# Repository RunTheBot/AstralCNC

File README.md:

# AstralCNC

A Replacement board for the Larken **StarCNC** controller. Built around the RPI Pico, this board is designed with safety and flexibility in mind, allowing for easy integration with external stepper drivers and digital inputs.

Powered by the Raspberry Pi Pico and GRBL-HAL.

Made to referbrish a Larken 24/24 router at my school that is over 25 years old.

# Features
- Supports up to 8 external stepper drivers (5v IO, Step/Dir)
- Supports up to 8 external digital inputs (3.3v IO)
- 5v IO can be switched to 3.3v IO
- 3.3v IO can be switched to 5v IO (for external stepper drivers)
- Built-in 12v regulator for powering all components
- Hardware level emergency stop
  - Emergency stop is not relient on software, ensuring that it works even if the software crashes as the stepper drivers put out a good ammount of EMI
- Hardware level reset button
  - Reset after an emergency stop is not relient on software, ensuring that the machine will remain stopped until it is manually reset
- 4 Analog inputs (ADC)
- All IO is PWM capable

# Images

# BOM

| Name                                           | Quantity | Single Unit Price | Total Price | URL/LCSC                                   | FALSE | Vendor (LCSC unless otheriwse indicated) |
|------------------------------------------------|----------|-------------------|-------------|--------------------------------------------|-------|------------------------------------------|
| Electronics                                    |          |                   |             |                                            | FALSE |                                          |
| 47pF                                           | 1        | N/A               | $0.29       | C105622                                    | FALSE |                                          |
| 0.1uF                                          | 1        | N/A               |             |                                            | FALSE | With My other two projects               |
| 22uF                                           | 2        | N/A               | $0.17       | C59461                                     | FALSE |                                          |
| 4.7uF                                          | 2        | N/A               | $0.15       | C69335                                     | FALSE |                                          |
| Molex_KK-254_AE-6410-02A_1x02_P2.54mm_Vertical | 1        | N/A               | $0.40       | C5447965                                   | FALSE |                                          |
| Molex_KK-254_AE-6410-10A_1x10_P2.54mm_Vertical | 1        | N/A               | $0.39       | C30169                                     | FALSE |                                          |
| PinHeader_2x04_P2.54mm_Vertical                | 1        | N/A               | $0.39       | C2829882                                   | FALSE |                                          |
| PinHeader_1x04_P2.54mm_Vertical                | 7        | N/A               | $0.42       | C2935910                                   | FALSE |                                          |
| Molex_KK-254_AE-6410-03A_1x03_P2.54mm_Vertical | 4        | N/A               | $0.71       | C29275                                     | FALSE |                                          |
| 6.8UH                                          | 1        | N/A               | $1.18       | C5296375                                   | FALSE |                                          |
| BC847                                          | 3        | N/A               | $0.46       | C57668                                     | FALSE |                                          |
| 220k                                           | 1        | N/A               | $0.10       | C22961                                     | FALSE |                                          |
| 41.2k                                          | 1        | N/A               | $0.10       | C2930101                                   | FALSE |                                          |
| 93.1k                                          | 1        | N/A               | $0.10       | C2933266                                   | FALSE |                                          |
| 22k                                            | 1        | N/A               | $0.09       | C2907015                                   | FALSE |                                          |
| 10k                                            | 6        | N/A               |             |                                            | FALSE | With My other two projects               |
| AP63357                                        | 1        | N/A               | $0.52       | C2158014                                   | FALSE |                                          |
| 74HC244                                        | 2        | N/A               | $0.77       | C5623                                      | FALSE |                                          |
| RP2350_Stamp                                   | 1        | N/A               | $12.05      | https://lectronz.com/products/rp2350-stamp | FALSE |                                          |
| TXS0108EPW                                     | 2        | N/A               | $1.12       | C17206                                     | FALSE |                                          |
| MOLEX 22013037                                 | 4        |                   | $0.27       | C22451182                                  | FALSE |                                          |
| Molex 2759 seris                               | 12       |                   | $0.24       | C22451180                                  | FALSE |                                          |
| PCB - JLC                                      |          |                   | $9.00       |                                            |       |                                          |
| LCSC - Shipping and handling                   |          |                   | $17.16      |                                            |       |                                          |
| lectronz                                       |          |                   | $17.79      |                                            |       |                                          |
| JLC - Shipping                                 |          |                   | $8.23       |                                            |       |                                          |
|                                                |          |                   |             |                                            |       |                                          |
|                                                |          |                   |             |                                            |       |                                          |
|                                                |          |                   |             |                                            |       |                                          |
|                                                |          |                   |             |                                            |       |                                          |
|                                                |          |                   |             |                                            |       |                                          |
|                                                |          |                   |             |                                            |       |                                          |
|                                                |          |                   |             |                                            |       |                                          |
|                                                |          |                   |             | CAD                                        |       |                                          |
|                                                |          |                   | $72.10      | USD                                        |       |                                          |
|                                                |          |                   | $72.10      | Total - USD                                |       |                                          |

Why is shipping so expensive? 😭

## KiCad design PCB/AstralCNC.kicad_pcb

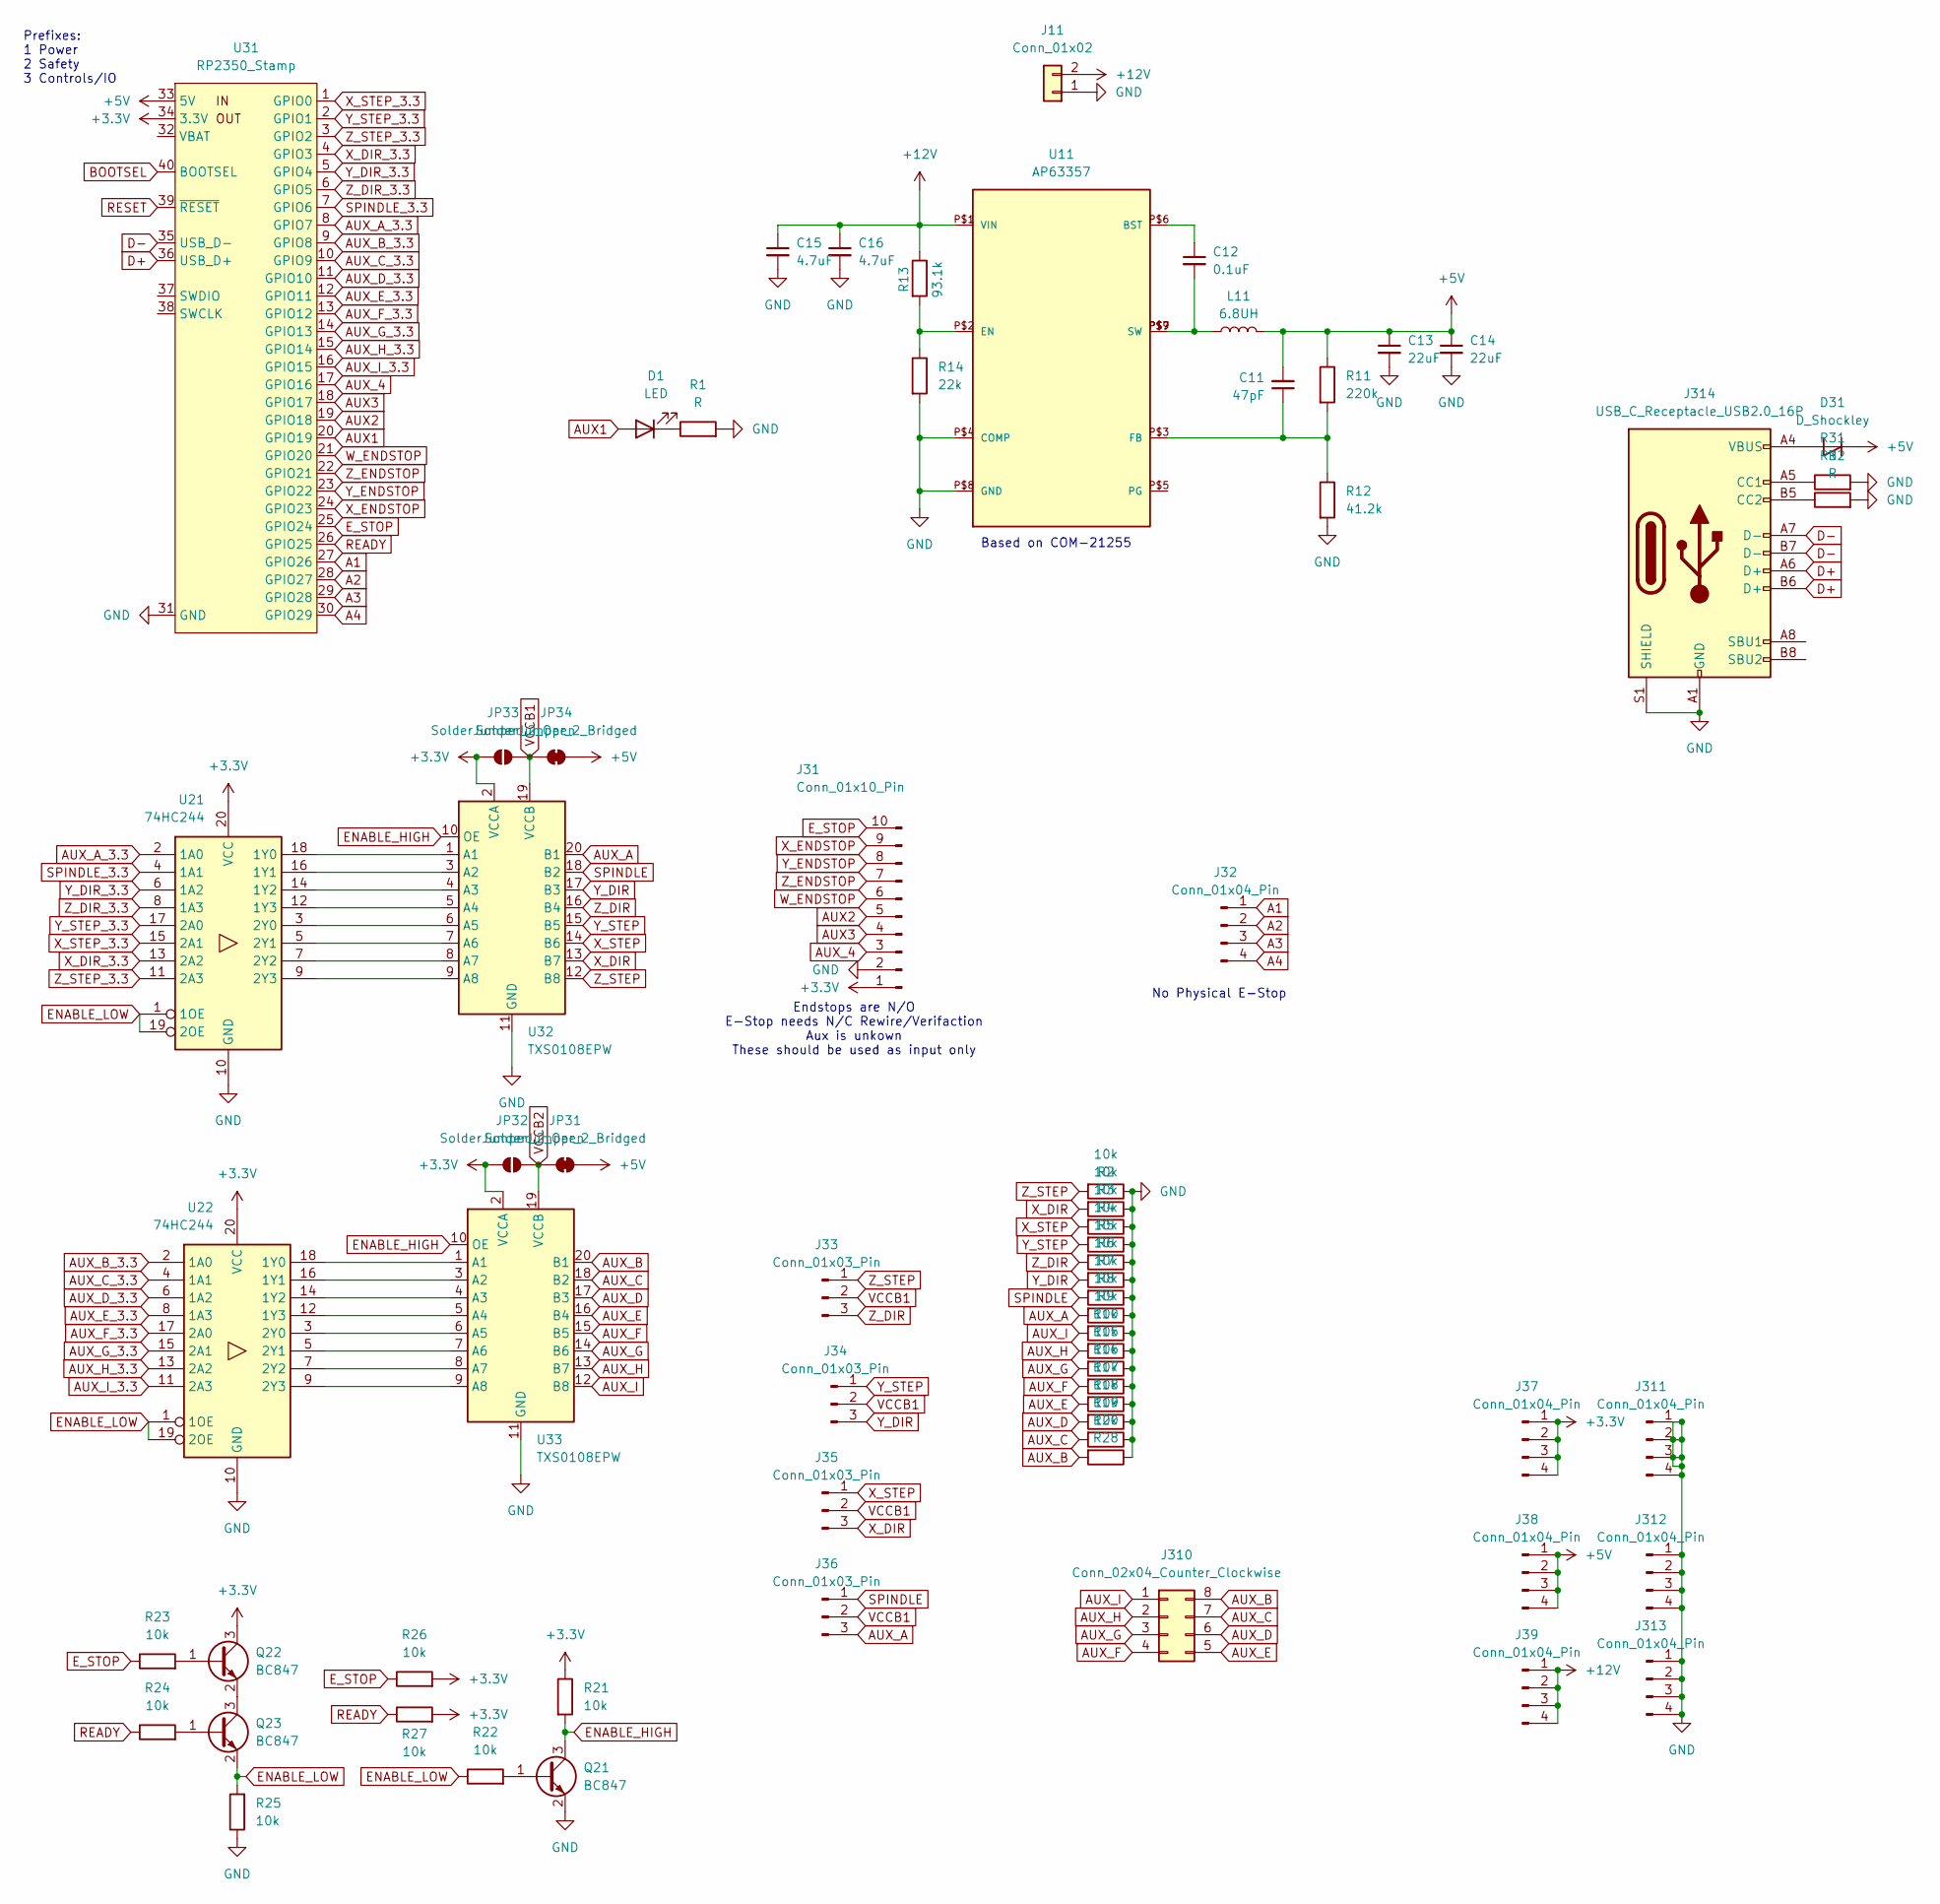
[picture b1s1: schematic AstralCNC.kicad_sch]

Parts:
C11: 47pF; C_0603_1608Metric_Pad1.08x0.95mm_HandSolder
C12: 0.1uF; C_0805_2012Metric_Pad1.18x1.45mm_HandSolder
C13, C14: 22uF; C_0603_1608Metric_Pad1.08x0.95mm_HandSolder
C15, C16: 4.7uF; C_0603_1608Metric_Pad1.08x0.95mm_HandSolder
D1: LED; PinHeader_1x02_P2.54mm_Vertical
D31: D_Shockley; D_SMA_Handsoldering
J11: Conn_01x02; Molex_KK-254_AE-6410-02A_1x02_P2.54mm_Vertical
J31: Conn_01x10_Pin; Molex_KK-254_AE-6410-10A_1x10_P2.54mm_Vertical
J32, J37, J38, J39, J311, J312, J313: Conn_01x04_Pin; PinHeader_1x04_P2.54mm_Vertical
J33, J34, J35, J36: Conn_01x03_Pin; Molex_KK-254_AE-6410-03A_1x03_P2.54mm_Vertical
J310: Conn_02x04_Counter_Clockwise; PinHeader_2x04_P2.54mm_Vertical
J314: USB_C_Receptacle_USB2.0_16P; USB_C_Receptacle_G-Switch_GT-USB-7010ASV
JP31, JP34: SolderJumper_2_Bridged; SolderJumper-2_P1.3mm_Bridged_RoundedPad1.0x1.5mm
JP32, JP33: SolderJumper_2_Open; SolderJumper-2_P1.3mm_Open_RoundedPad1.0x1.5mm
L11: 6.8UH; L_Chilisin_BMRA00050530
Q21, Q22, Q23: BC847; SOT-23
R1, R31, R32: R; C_0603_1608Metric_Pad1.08x0.95mm_HandSolder
R2, R3, R4, R5, R6, R7, R8, R9, R10, R15, R16, R17, R18, R19, R20, R21, R22, R23, R24, R25, R26, R27, R28: 10k; C_0603_1608Metric_Pad1.08x0.95mm_HandSolder
R11: 220k; C_0603_1608Metric_Pad1.08x0.95mm_HandSolder
R12: 41.2k; C_0603_1608Metric_Pad1.08x0.95mm_HandSolder
R13: 93.1k; C_0603_1608Metric_Pad1.08x0.95mm_HandSolder
R14: 22k; C_0603_1608Metric_Pad1.08x0.95mm_HandSolder
U11: AP63357; V-DFN3020-13
U21, U22: 74HC244; TSSOP-20_4.4x6.5mm_P0.65mm
U31: RP2350_Stamp; RP2xxx_Stamp_THT
U32, U33: TXS0108EPW; TSSOP-20_4.4x6.5mm_P0.65mm

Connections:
+3.3V: J31.1, J37.1, J37.2, J37.3, J37.4, JP32.1 (A), JP33.1 (A), Q22.3 (C), R21.1, R26.2, R27.2, U21.20 (VCC), U22.20 (VCC), U31.34 (3.3V), U32.2 (VCCA), U33.2 (VCCA)
+5V: C11.2, C13.1, C14.1, D31.1 (K), J38.1, J38.2, J38.3, J38.4, JP31.2 (B), JP34.2 (B), L11.2, R11.1, U31.33 (5V)
+12V: C15.1, C16.1, J11.2, J39.1, J39.2, J39.3, J39.4, R13.1, U11.P$1 (VIN)
A1: J32.1, U31.27 (GPIO26)
A2: J32.2, U31.28 (GPIO27)
A3: J32.3, U31.29 (GPIO28)
A4: J32.4, U31.30 (GPIO29)
AUX1: D1.2 (A), U31.20 (GPIO19)
AUX2: J31.5, U31.19 (GPIO18)
AUX3: J31.4, U31.18 (GPIO17)
AUX_4: J31.3, U31.17 (GPIO16)
AUX_A: J36.3, R9.2, U32.20 (B1)
AUX_A_3.3: U21.2 (1A0), U31.8 (GPIO7)
AUX_B: J310.8, R28.2, U33.20 (B1)
AUX_B_3.3: U22.2 (1A0), U31.9 (GPIO8)
AUX_C: J310.7, R20.2, U33.18 (B2)
AUX_C_3.3: U22.4 (1A1), U31.10 (GPIO9)
AUX_D: J310.6, R19.2, U33.17 (B3)
AUX_D_3.3: U22.6 (1A2), U31.11 (GPIO10)
AUX_E: J310.5, R18.2, U33.16 (B4)
AUX_E_3.3: U22.8 (1A3), U31.12 (GPIO11)
AUX_F: J310.4, R17.2, U33.15 (B5)
AUX_F_3.3: U22.17 (2A0), U31.13 (GPIO12)
AUX_G: J310.3, R16.2, U33.14 (B6)
AUX_G_3.3: U22.15 (2A1), U31.14 (GPIO13)
AUX_H: J310.2, R15.2, U33.13 (B7)
AUX_H_3.3: U22.13 (2A2), U31.15 (GPIO14)
AUX_I: J310.1, R10.2, U33.12 (B8)
AUX_I_3.3: U22.11 (2A3), U31.16 (GPIO15)
BOOTSEL: U31.40 (BOOTSEL)
D+: J314.A6 (D+), J314.B6 (D+), U31.36 (USB_D+)
D-: J314.A7 (D-), J314.B7 (D-), U31.35 (USB_D-)
ENABLE_HIGH: Q21.3 (C), R21.2, U32.10 (OE), U33.10 (OE)
ENABLE_LOW: Q23.2 (E), R22.1, R25.2, U21.1 (1OE), U21.19 (2OE), U22.1 (1OE), U22.19 (2OE)
E_STOP: J31.10, R23.1, R26.1, U31.25 (GPIO24)
GND: C13.2, C14.2, C15.2, C16.2, J11.1, J31.2, J311.1, J311.2, J311.3, J311.4, J312.1, J312.2, J312.3, J312.4, J313.1, J313.2, J313.3, J313.4, J314.A1 (GND), J314.A12 (GND), J314.B1 (GND), J314.B12 (GND), J314.S1 (SHIELD), Q21.2 (E), R1.2, R2.1, R3.1, R4.1, R5.1, R6.1, R7.1, R8.1, R9.1, R10.1, R12.2, R14.2, R15.1, R16.1, R17.1, R18.1, R19.1, R20.1, R25.1, R28.1, R31.2, R32.2, U11.P$4 (COMP), U11.P$8 (GND), U21.10 (GND), U22.10 (GND), U31.31 (GND), U32.11 (GND), U33.11 (GND)
unnamed: C12.2, L11.1, U11.P$7 (SW), U11.P$9 (SW)
unnamed: D1.1 (K), R1.1
unnamed: D31.2 (A), J314.A4 (VBUS), J314.A9 (VBUS), J314.B4 (VBUS), J314.B9 (VBUS)
unnamed: J314.A5 (CC1), R31.1
unnamed: J314.B5 (CC2), R32.1
unnamed: Q21.1 (B), R22.2
unnamed: Q22.1 (B), R23.2
unnamed: Q22.2 (E), Q23.3 (C)
unnamed: Q23.1 (B), R24.2
unnamed: C12.1, U11.P$6 (BST)
unnamed: R13.2, R14.1, U11.P$2 (EN)
unnamed: C11.1, R11.2, R12.1, U11.P$3 (FB)
unnamed: U21.18 (1Y0), U32.1 (A1)
unnamed: U21.16 (1Y1), U32.3 (A2)
unnamed: U21.14 (1Y2), U32.4 (A3)
unnamed: U21.12 (1Y3), U32.5 (A4)
unnamed: U21.3 (2Y0), U32.6 (A5)
unnamed: U21.5 (2Y1), U32.7 (A6)
unnamed: U21.7 (2Y2), U32.8 (A7)
unnamed: U21.9 (2Y3), U32.9 (A8)
unnamed: U22.18 (1Y0), U33.1 (A1)
unnamed: U22.16 (1Y1), U33.3 (A2)
unnamed: U22.14 (1Y2), U33.4 (A3)
unnamed: U22.12 (1Y3), U33.5 (A4)
unnamed: U22.3 (2Y0), U33.6 (A5)
unnamed: U22.5 (2Y1), U33.7 (A6)
unnamed: U22.7 (2Y2), U33.8 (A7)
unnamed: U22.9 (2Y3), U33.9 (A8)
READY: R24.1, R27.1, U31.26 (GPIO25)
RESET: U31.39 (~RESET)
SPINDLE: J36.1, R8.2, U32.18 (B2)
SPINDLE_3.3: U21.4 (1A1), U31.7 (GPIO6)
VCCB1: J33.2, J34.2, J35.2, J36.2, JP33.2 (B), JP34.1 (A), U32.19 (VCCB)
VCCB2: JP31.1 (A), JP32.2 (B), U33.19 (VCCB)
W_ENDSTOP: J31.6, U31.21 (GPIO20)
X_DIR: J35.3, R3.2, U32.13 (B7)
X_DIR_3.3: U21.13 (2A2), U31.4 (GPIO3)
X_ENDSTOP: J31.9, U31.24 (GPIO23)
X_STEP: J35.1, R4.2, U32.14 (B6)
X_STEP_3.3: U21.15 (2A1), U31.1 (GPIO0)
Y_DIR: J34.3, R7.2, U32.17 (B3)
Y_DIR_3.3: U21.6 (1A2), U31.5 (GPIO4)
Y_ENDSTOP: J31.8, U31.23 (GPIO22)
Y_STEP: J34.1, R5.2, U32.15 (B5)
Y_STEP_3.3: U21.17 (2A0), U31.2 (GPIO1)
Z_DIR: J33.3, R6.2, U32.16 (B4)
Z_DIR_3.3: U21.8 (1A3), U31.6 (GPIO5)
Z_ENDSTOP: J31.7, U31.22 (GPIO21)
Z_STEP: J33.1, R2.2, U32.12 (B8)
Z_STEP_3.3: U21.11 (2A3), U31.3 (GPIO2)

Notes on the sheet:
Prefixes: 1 Power 2 Safety 3 Controls/IO
Endstops are N/O E-Stop needs N/C Rewire/Verifaction Aux is unkown These should be used as input only
No Physical E-Stop
Based on COM-21255

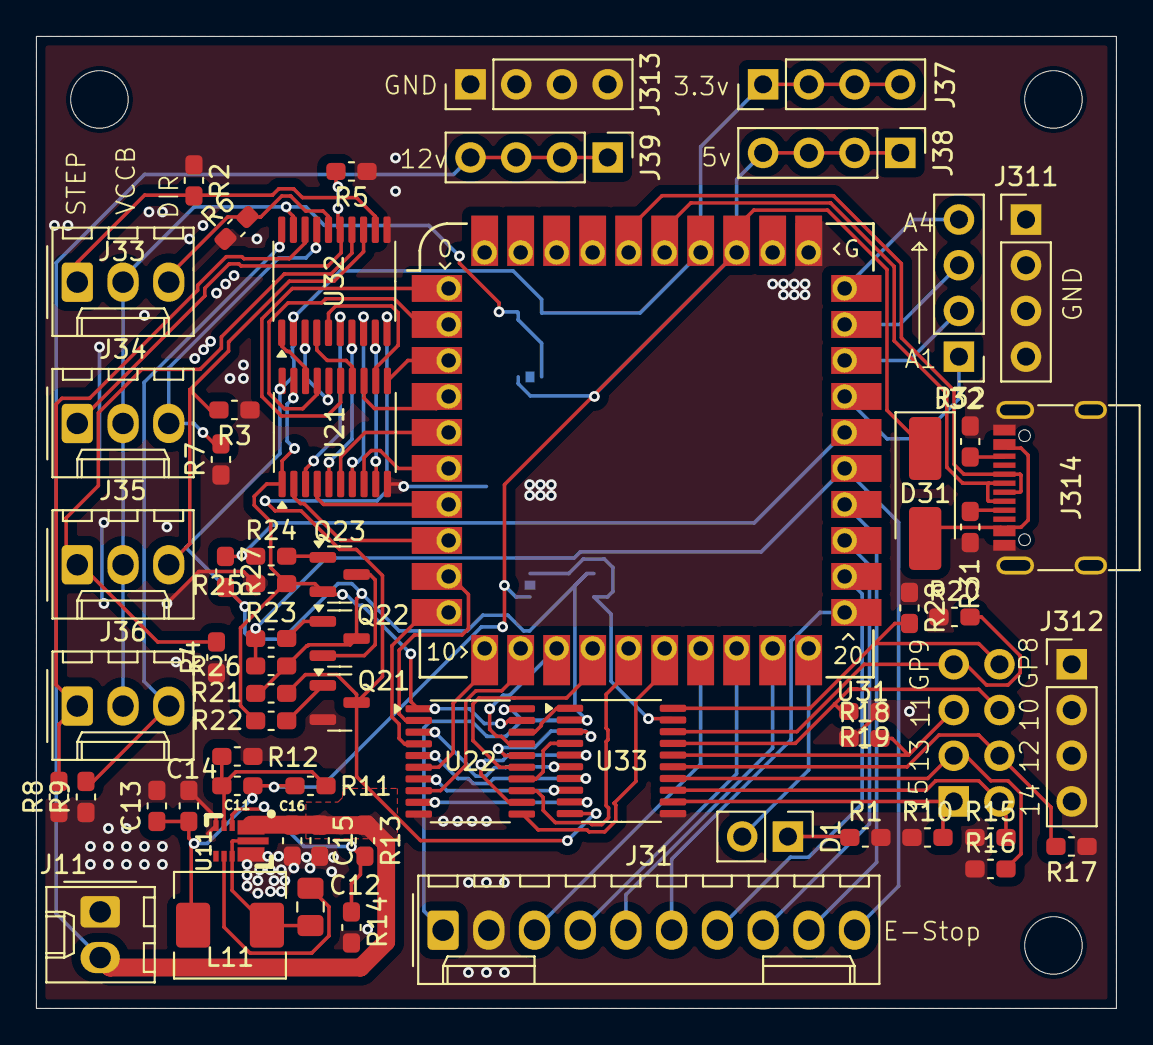
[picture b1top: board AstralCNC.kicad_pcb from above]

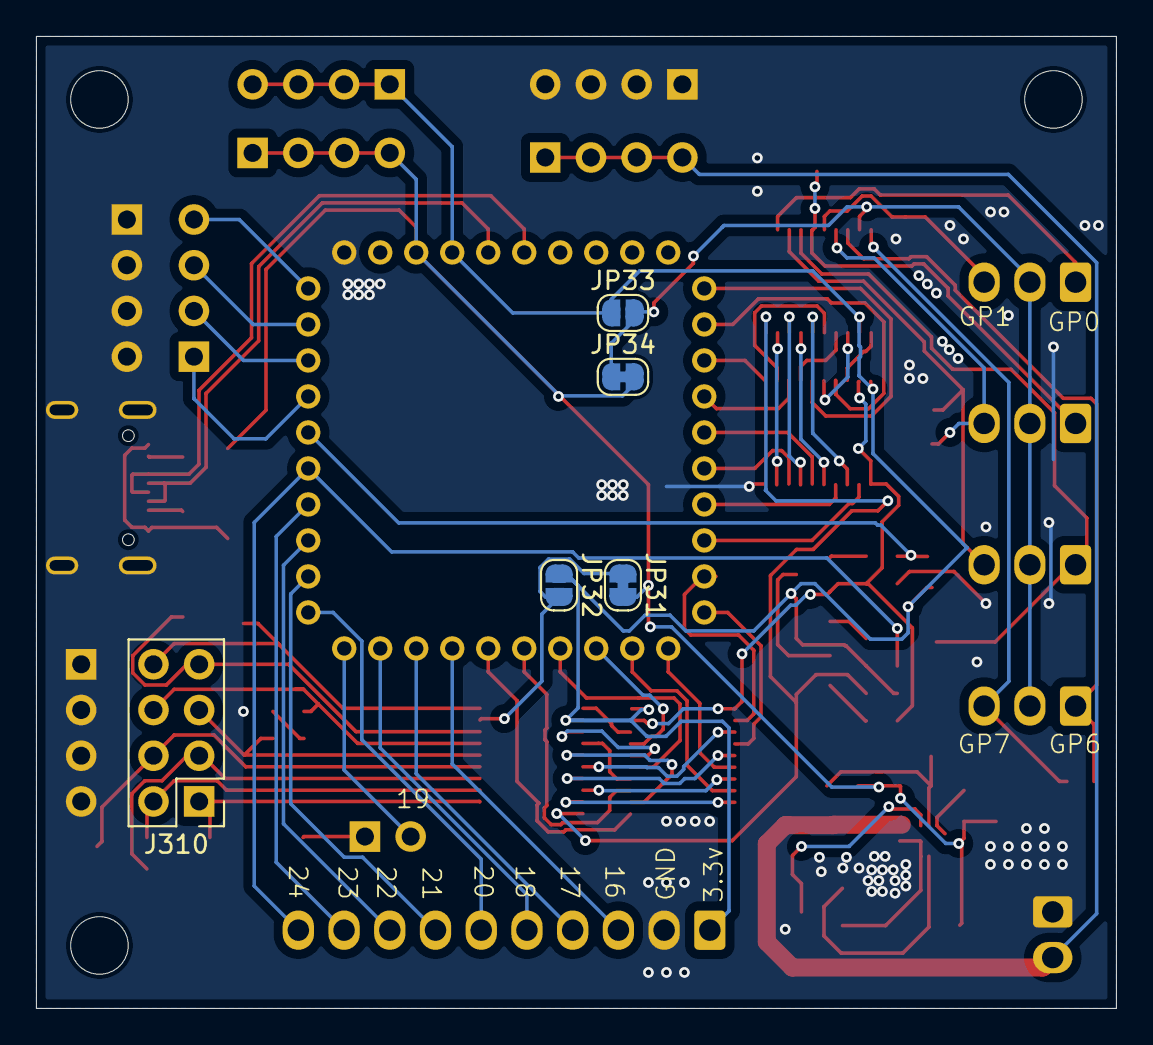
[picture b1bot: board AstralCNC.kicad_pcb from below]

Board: 2 copper layers, 60.0 x 54.0 mm, 67 parts (5 on the bottom side), 84 nets.

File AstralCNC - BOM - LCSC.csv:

Name,Quantity,Single Unit Price,Total Price,URL/LCSC,FALSE,Vendor (LCSC unless otheriwse indicated)
Electronics,,,,,FALSE,
47pF,1,N/A,$0.29,C105622,FALSE,
0.1uF,1,N/A,,,FALSE,With My other two projects
22uF,2,N/A,$0.17,C59461,FALSE,
4.7uF,2,N/A,$0.15,C69335,FALSE,
Molex_KK-254_AE-6410-02A_1x02_P2.54mm_Vertical,1,N/A,$0.40,C5447965,FALSE,
Molex_KK-254_AE-6410-10A_1x10_P2.54mm_Vertical,1,N/A,$0.39,C30169,FALSE,
PinHeader_2x04_P2.54mm_Vertical,1,N/A,$0.39,C2829882,FALSE,
PinHeader_1x04_P2.54mm_Vertical,7,N/A,$0.42,C2935910,FALSE,
Molex_KK-254_AE-6410-03A_1x03_P2.54mm_Vertical,4,N/A,$0.71,C29275,FALSE,
6.8UH,1,N/A,$1.18,C5296375,FALSE,
BC847,3,N/A,$0.46,C57668,FALSE,
220k,1,N/A,$0.10,C22961,FALSE,
41.2k,1,N/A,$0.10,C2930101,FALSE,
93.1k,1,N/A,$0.10,C2933266,FALSE,
22k,1,N/A,$0.09,C2907015,FALSE,
10k,6,N/A,,,FALSE,With My other two projects
AP63357,1,N/A,$0.52,C2158014,FALSE,
74HC244,2,N/A,$0.77,C5623,FALSE,
RP2350_Stamp,1,N/A,$12.05,https://lectronz.com/products/rp2350-stamp,FALSE,
TXS0108EPW,2,N/A,$1.12,C17206,FALSE,
MOLEX 22013037,4,,$0.27,C22451182,FALSE,
Molex 2759 seris,12,,$0.24,C22451180,FALSE,
PCB - JLC,,,$9.00,,,
LCSC - Shipping and handling,,,$17.16,,,
lectronz,,,$17.79,,,
JLC - Shipping,,,$8.23,,,
,,,,,,
,,,,,,
,,,,,,
,,,,,,
,,,,,,
,,,,,,
,,,,,,
,,,,CAD,,
,,,$72.10,USD,,
,,,$72.10,Total - USD,,

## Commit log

2025-06-20 Add initial files for AstralCNC project
    - Created positions.csv for component placement data.
    - Added sym-lib-table for symbol library references.
    - Introduced lock files for PCB and schematic to manage editing sessions.
    - Added README.md with project overview, features, images, and BOM.
    - Created journal.md to document project progress and development notes.
2025-06-20 More time designing
2025-06-20 Add June 17 entry with software exploration for CNC control options
2025-06-20 Update journal entries: Adjusted hours for June 17 and June 19, added USB-C connector details, and included an image for clarity.
2025-06-20 bruh
2025-06-22 Add submodule for AstralCNC-grblHAL and update backup files
2025-06-22 Added pull downs for safety
